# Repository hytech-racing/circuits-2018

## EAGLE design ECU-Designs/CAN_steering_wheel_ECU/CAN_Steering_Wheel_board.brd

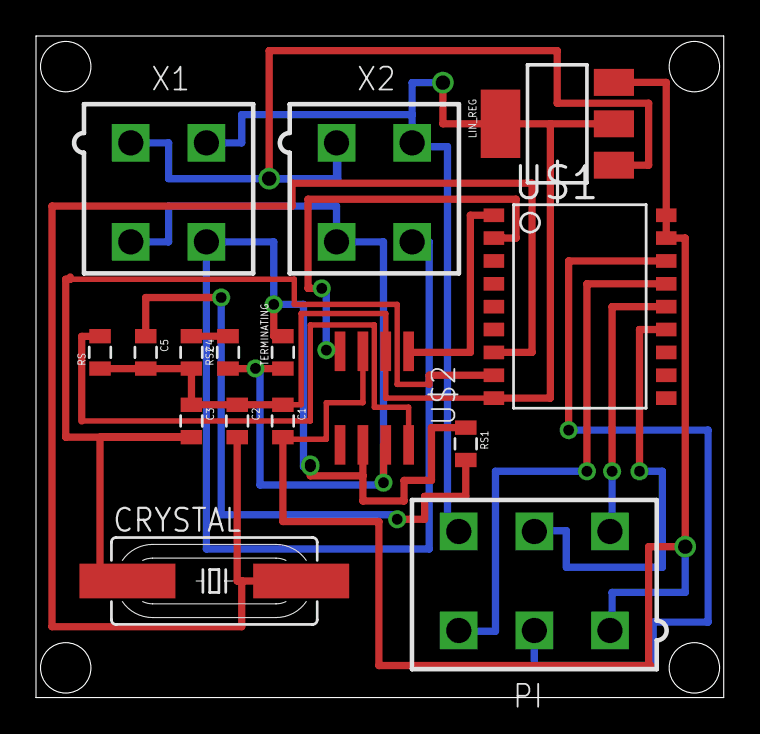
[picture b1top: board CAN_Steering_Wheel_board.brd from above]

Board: 2 copper layers, 38.2 x 36.8 mm, 16 parts (0 on the bottom side), 16 nets.

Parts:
C1: 0.1uF; 0805
C2, C3: 22pF; 0805
C4, C5: 560pF; 0805
CRYSTAL: 16MHz; HC49UP
LIN_REG: SOT223
PI: MINIFIT_5566-6
RS: 4.7k; 0805
RS1, RS2: 100; 0805
TERMINATING: 120; 0805
U$1: MCP2515SMD; SOIC-18W
U$2: MCP2551; SOIC-08
X1, X2: MINIFIT_5566-4

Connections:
5V: C1.2, LIN_REG.3, PI.1, U$1.17, U$1.18, U$2.3
12V: LIN_REG.1, X1.1, X2.1
CANH: RS2.1, TERMINATING.1, U$2.7, X1.3, X2.3
CANL: RS1.1, TERMINATING.2, U$2.6, X1.4, X2.4
GND: C1.1, C2.1, C3.1, C4.2, C5.2, LIN_REG.2, LIN_REG.4, PI.6, RS.1, U$1.9, U$2.2, X1.2, X2.2
unnamed: U$1.1, U$2.1
unnamed: U$1.2, U$2.4
unnamed: C3.2, CRYSTAL.1, U$1.8
unnamed: PI.2, U$1.16
unnamed: PI.3, U$1.15
unnamed: PI.4, U$1.14
unnamed: PI.5, U$1.13
unnamed: RS.2, U$2.8
unnamed: C2.2, CRYSTAL.2, U$1.7
unnamed: C4.1, RS2.2
unnamed: C5.1, RS1.2

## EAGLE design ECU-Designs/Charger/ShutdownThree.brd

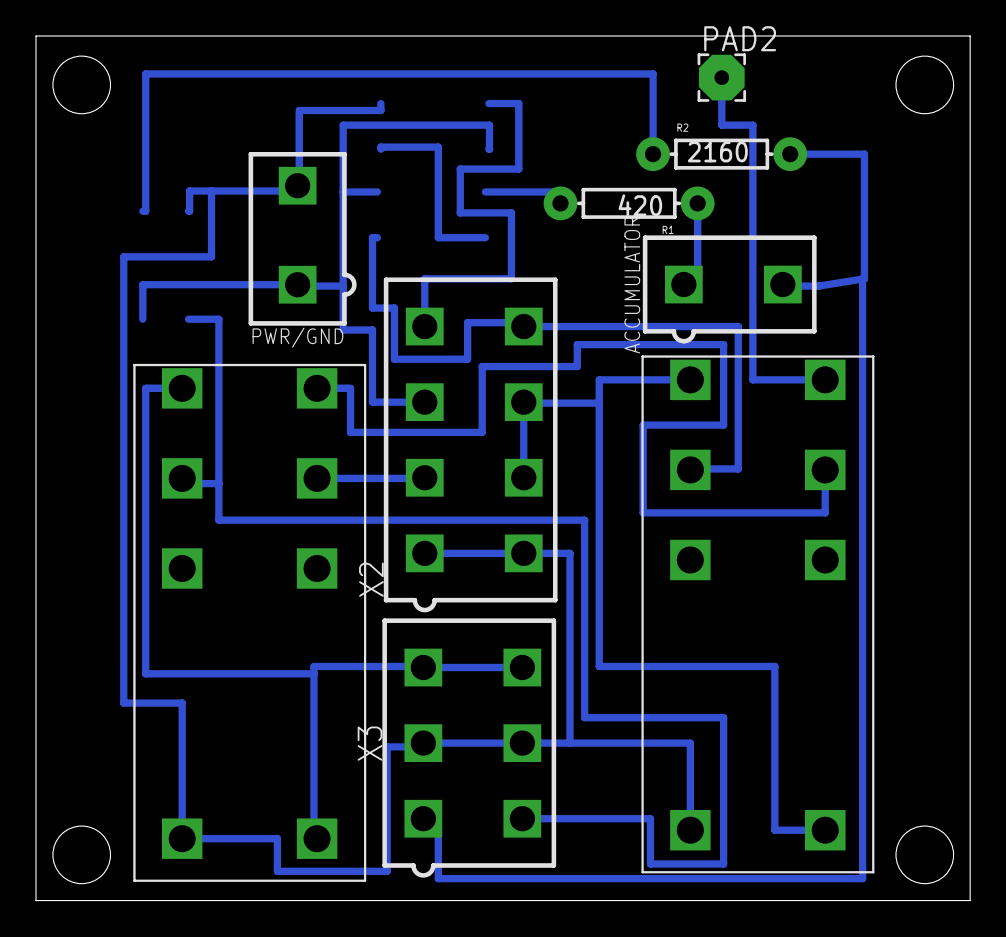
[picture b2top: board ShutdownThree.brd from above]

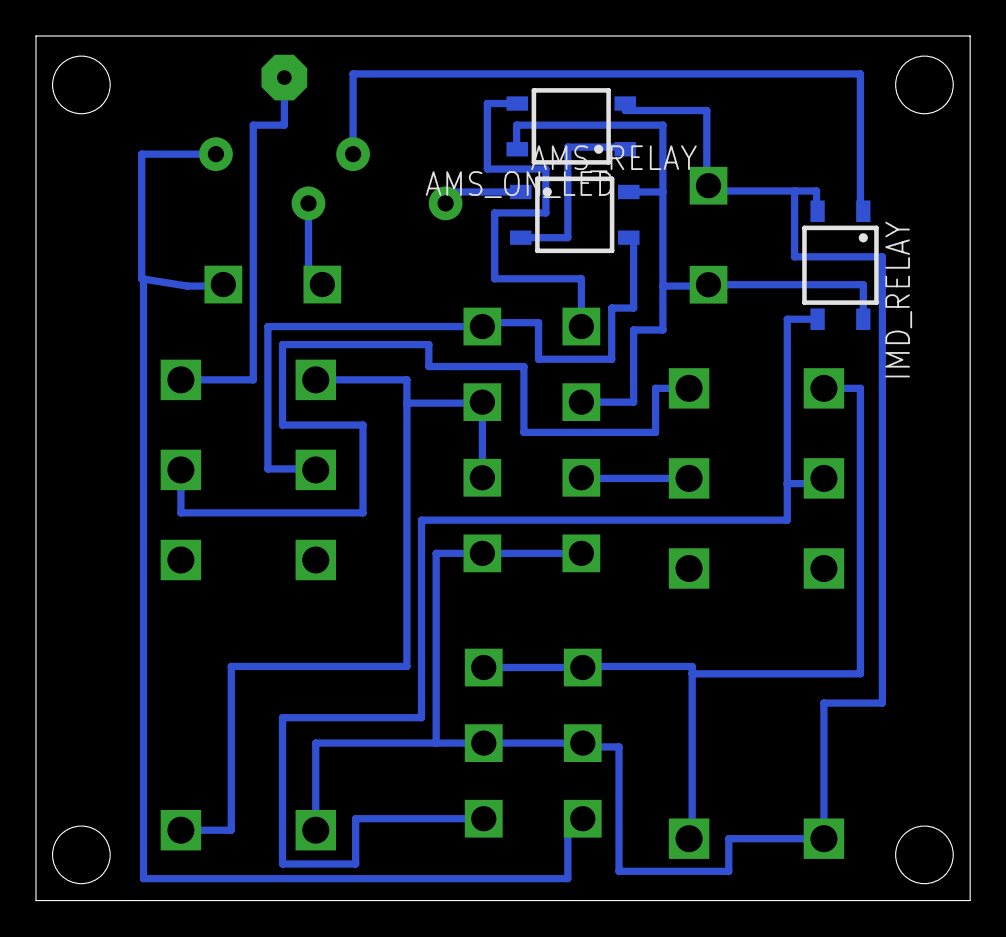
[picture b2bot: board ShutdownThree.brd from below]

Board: 2 copper layers, 51.9 x 48.0 mm, 12 parts (3 on the bottom side), 15 nets.

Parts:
ACCUMULATOR: CONNECTOR-2; MINIFIT_5566-2
AMS_ON_LED: CPC1002N; SOP04
AMS_RELAY: CPC1002N; SOP04
IMD: G2RL-2-DC12; G2RL-2
IMD_RELAY: CPC1002N; SOP04
PAD2: WIREPAD2,54/0,8; 2,54/0,8
PWR/GND: MINIFIT_5566-2
R1: 420; AXIAL-0.3EZ
R2: 2160; AXIAL-0.3EZ
U$7: G2RL-2-DC12; G2RL-2
X2: CONNECTOR-8; MINIFIT_5566-8
X3: CONNECTOR-6; MINIFIT_5566-6

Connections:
+12V: AMS_ON_LED.4, AMS_RELAY.4, IMD_RELAY.4, PWR/GND.1, X2.3
AMS: ACCUMULATOR.1, R1.P$1
GND: AMS_ON_LED.2, IMD.COIL+, IMD_RELAY.2, PWR/GND.2, U$7.COIL+, X2.1, X2.5, X3.2, X3.5
IMD: ACCUMULATOR.2, R2.P$2, X3.1
unnamed: IMD.6, X2.2
unnamed: IMD.5, U$7.6
unnamed: AMS_ON_LED.3, X2.4
unnamed: AMS_RELAY.1, R1.P$2
unnamed: AMS_RELAY.3, U$7.3, X2.8
unnamed: PAD2.1, U$7.5
unnamed: IMD.3, IMD_RELAY.3, X3.4
unnamed: IMD_RELAY.1, R2.P$1
unnamed: U$7.4, U$7.COIL-, X2.6, X2.7
unnamed: IMD.4, IMD.COIL-, X3.3, X3.6
unnamed: AMS_ON_LED.1, AMS_RELAY.2

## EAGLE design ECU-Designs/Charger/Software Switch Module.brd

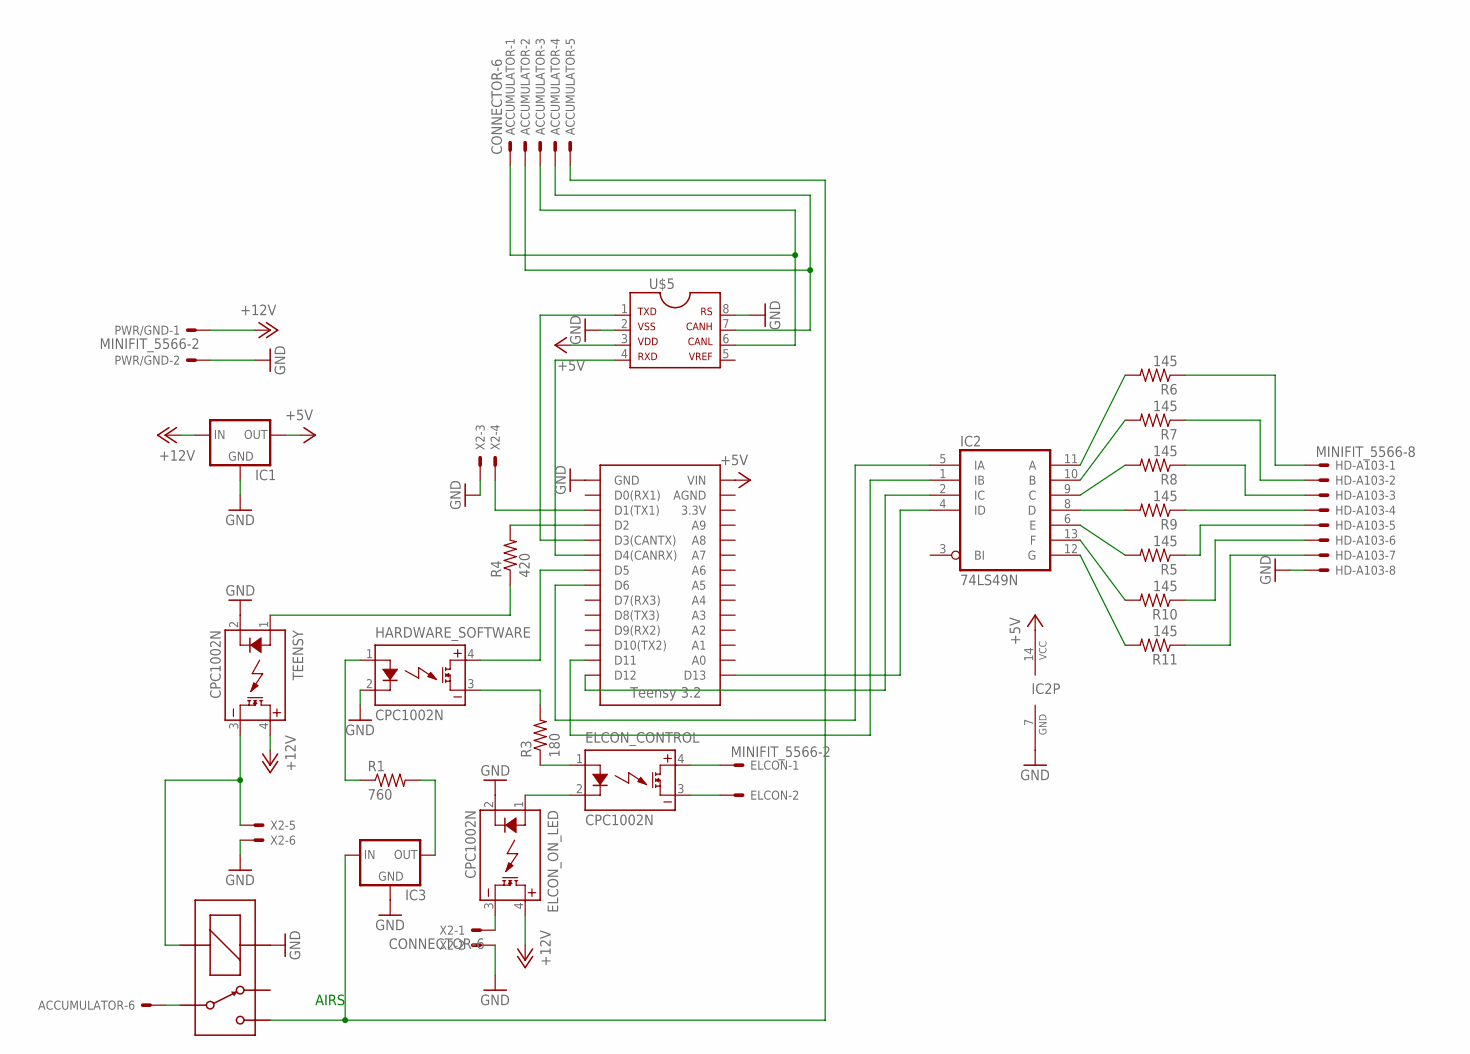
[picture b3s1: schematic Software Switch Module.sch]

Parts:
ACCUMULATOR: CONNECTOR-6; MINIFIT_5566-6
ELCON: MINIFIT_5566-2
ELCON_CONTROL: CPC1002N; SOP04
ELCON_ON_LED: CPC1002N; SOP04
HARDWARE_SOFTWARE: CPC1002N; SOP04
HD-A103: MINIFIT_5566-8
IC1, IC3: 5VREG_L7805_VERT; TO-220
IC2: 74LS49N; DIL14
PWR/GND: MINIFIT_5566-2
R1: 760; AXIAL-0.3
R3: 180; AXIAL-0.3EZ
R4: 420; AXIAL-0.3EZ
R5, R6, R7, R8, R9, R10, R11: 145; AXIAL-0.3EZ
TEENSY: CPC1002N; SOP04
U$1: TEENSY_3.2_SIMPLE
U$2: G5LE; ZF112
U$5: MCP2551; SOIC-08
X2: CONNECTOR-6; MINIFIT_5566-6

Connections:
+5V: IC1.3 (OUT), IC2.14 (VCC), U$1.VIN, U$5.3
+12V: ELCON_ON_LED.4 (DC+), IC1.1 (IN), PWR/GND.1, TEENSY.4 (DC+)
AIRS: ACCUMULATOR.5, IC3.1 (IN), U$2.S
GND: ELCON_ON_LED.2 (CONTROL-), HARDWARE_SOFTWARE.2 (CONTROL-), HD-A103.8, IC1.2 (GND), IC2.7 (GND), IC3.2 (GND), PWR/GND.2, TEENSY.2 (CONTROL-), U$1.GND, U$2.1 (COIL+), U$5.2, U$5.8, X2.2, X2.3, X2.6
unnamed: R4.P$1 (1), TEENSY.1 (CONTROL+)
unnamed: HARDWARE_SOFTWARE.1 (CONTROL+), R1.P$1 (1)
unnamed: HARDWARE_SOFTWARE.4 (DC+), U$1.D5
unnamed: ACCUMULATOR.6, U$2.P
unnamed: IC3.3 (OUT), R1.P$2 (2)
unnamed: ELCON_CONTROL.1 (CONTROL+), R3.P$1 (1)
unnamed: ELCON.1, ELCON_CONTROL.4 (DC+)
unnamed: ELCON.2, ELCON_CONTROL.3 (DC-)
unnamed: U$1.D1(TX1), X2.4
unnamed: U$1.D4(CANRX), U$5.4
unnamed: R4.P$2 (2), U$1.D2
unnamed: U$1.D3(CANTX), U$5.1
unnamed: ACCUMULATOR.1, ACCUMULATOR.3, U$5.6
unnamed: TEENSY.3 (DC-), U$2.2 (COIL-), X2.5
unnamed: IC2.11 (A), R6.P$2 (2)
unnamed: HARDWARE_SOFTWARE.3 (DC-), R3.P$2 (2)
unnamed: ELCON_CONTROL.2 (CONTROL-), ELCON_ON_LED.1 (CONTROL+)
unnamed: ELCON_ON_LED.3 (DC-), X2.1
unnamed: IC2.5 (IA), U$1.D6
unnamed: IC2.1 (IB), U$1.D11
unnamed: IC2.4 (ID), U$1.D13
unnamed: IC2.2 (IC), U$1.D12
unnamed: IC2.10 (B), R7.P$2 (2)
unnamed: IC2.9 (C), R8.P$2 (2)
unnamed: IC2.8 (D), R9.P$2 (2)
unnamed: IC2.13 (F), R10.P$2 (2)
unnamed: IC2.12 (G), R11.P$2 (2)
unnamed: IC2.6 (E), R5.P$2 (2)
unnamed: HD-A103.1, R6.P$1 (1)
unnamed: ACCUMULATOR.2, ACCUMULATOR.4, U$5.7
unnamed: HD-A103.2, R7.P$1 (1)
unnamed: HD-A103.3, R8.P$1 (1)
unnamed: HD-A103.4, R9.P$1 (1)
unnamed: HD-A103.5, R5.P$1 (1)
unnamed: HD-A103.6, R10.P$1 (1)
unnamed: HD-A103.7, R11.P$1 (1)

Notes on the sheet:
AIRS

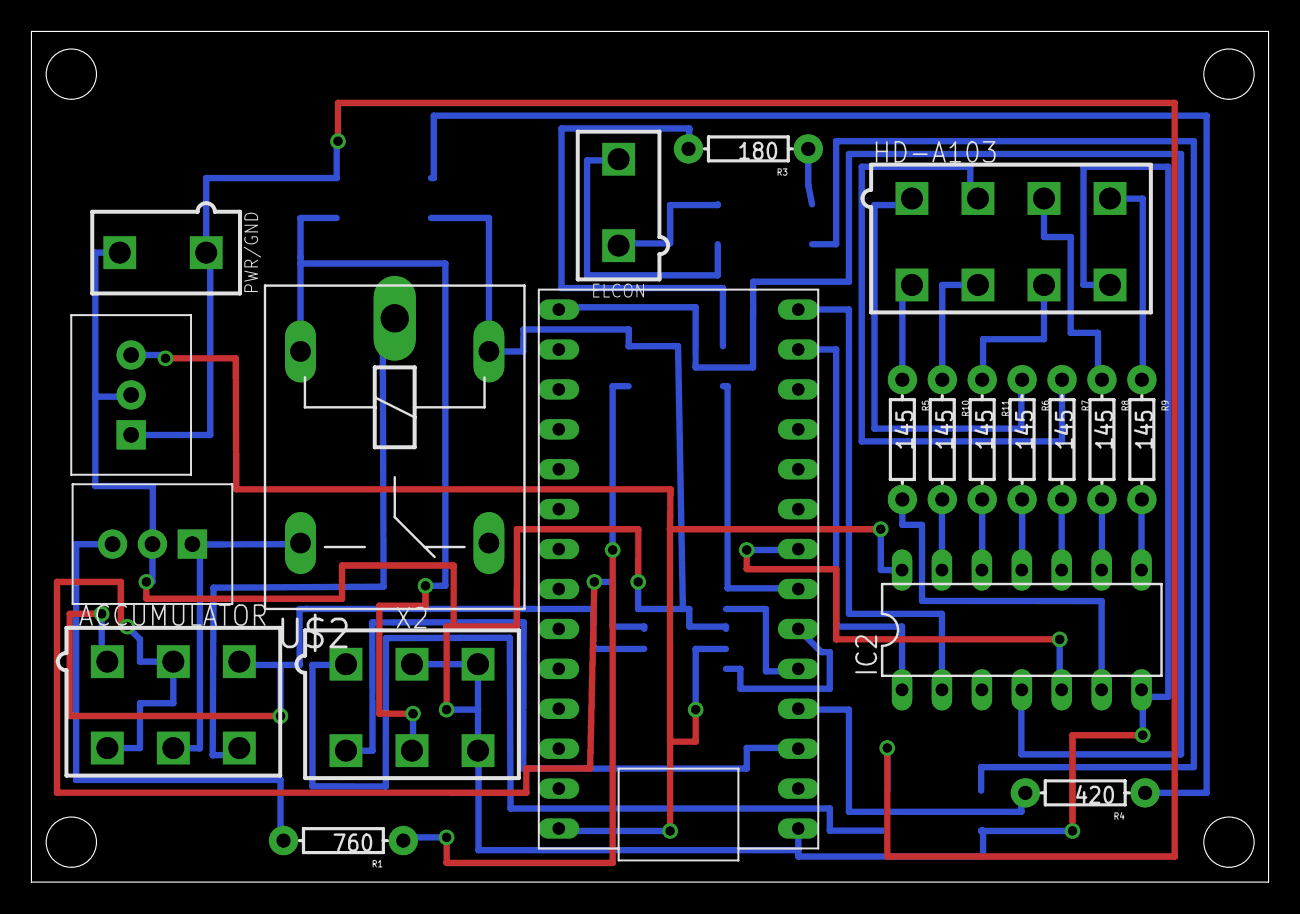
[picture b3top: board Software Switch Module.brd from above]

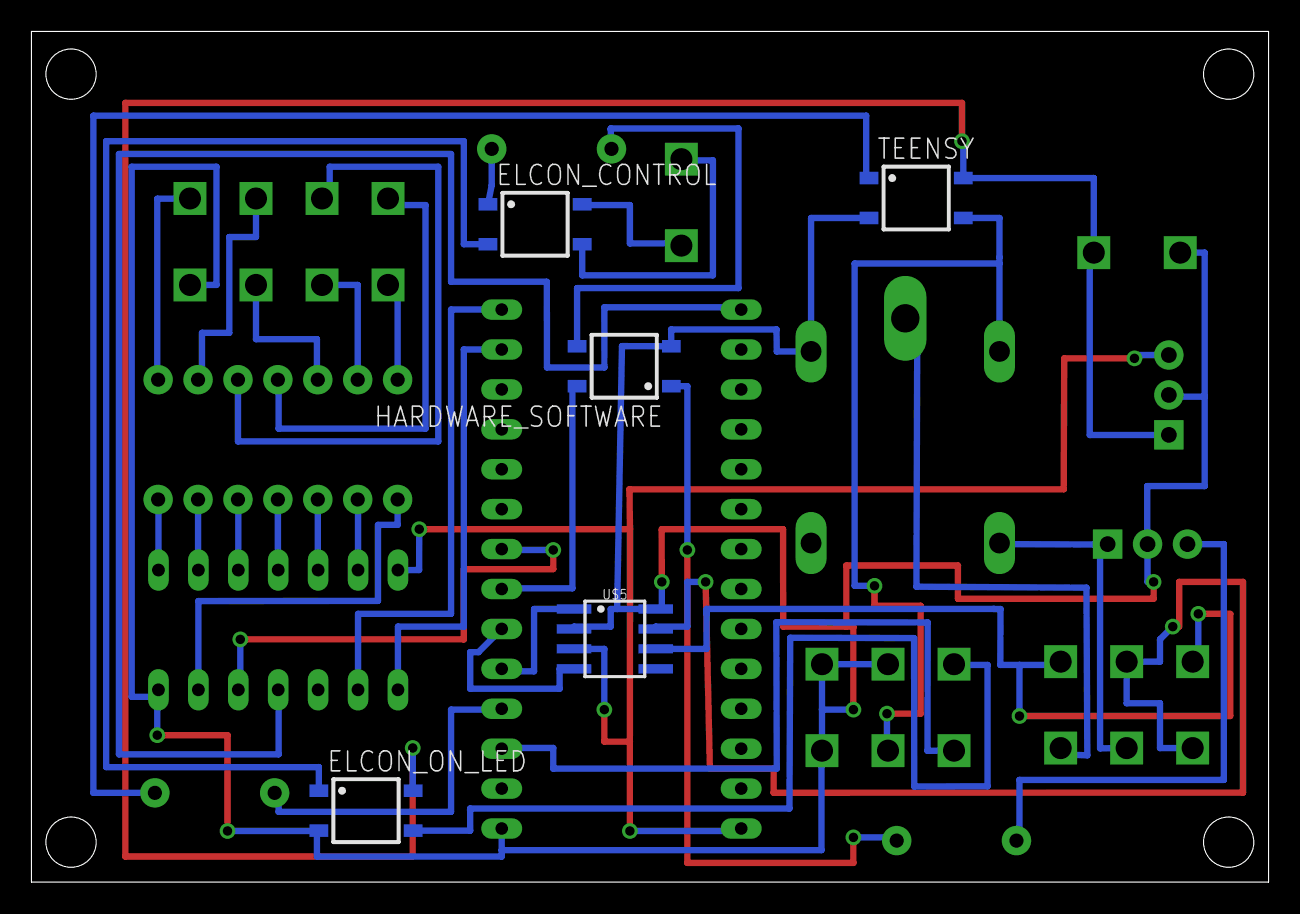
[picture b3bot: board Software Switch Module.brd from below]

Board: 2 copper layers, 78.7 x 54.1 mm, 25 parts (5 on the bottom side), 40 nets.

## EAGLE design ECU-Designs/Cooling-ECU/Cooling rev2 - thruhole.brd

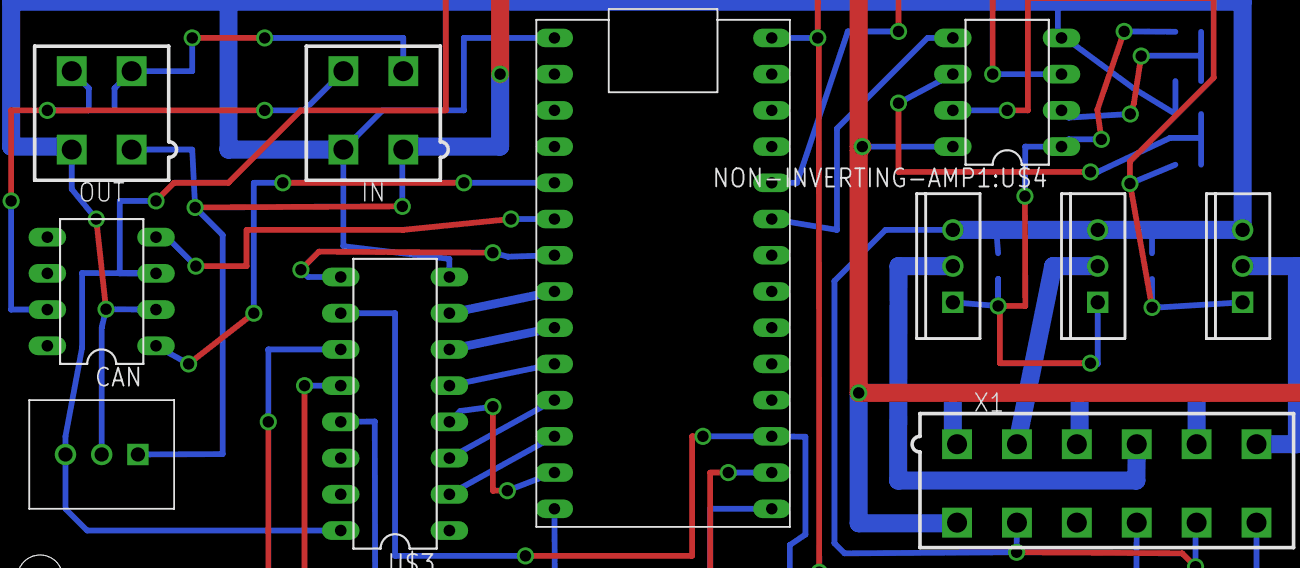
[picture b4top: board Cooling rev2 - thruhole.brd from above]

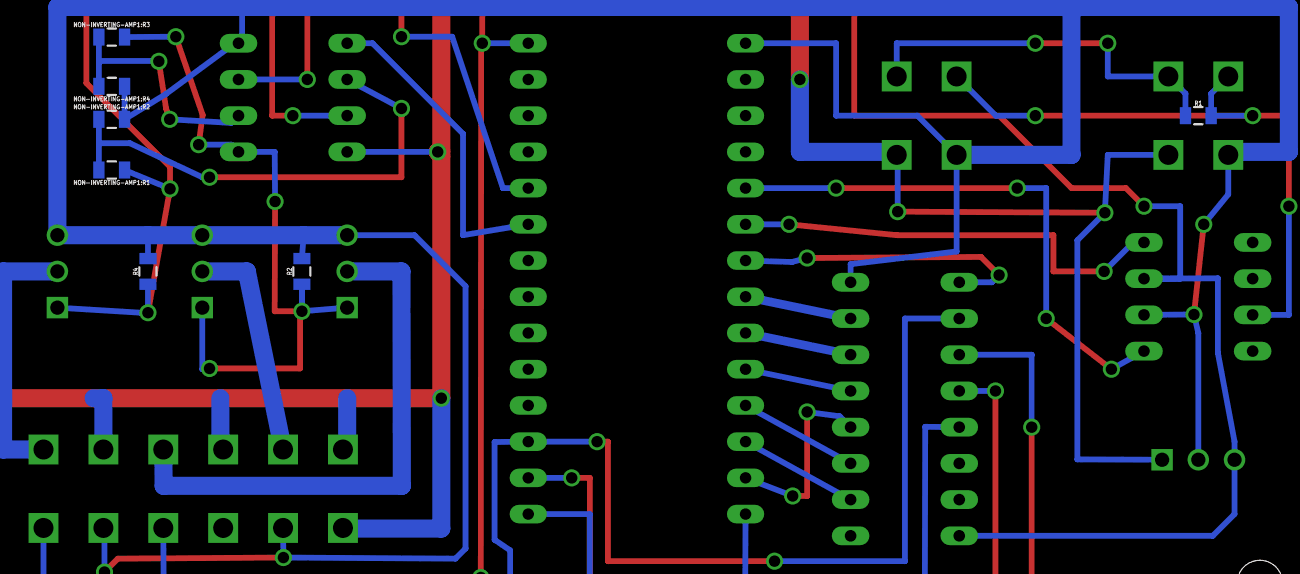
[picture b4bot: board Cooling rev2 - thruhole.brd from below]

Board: 2 copper layers, 18 parts (7 on the bottom side), 27 nets.

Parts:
CAN: MCP2551DIL; DIL08
IC1: TO-220-SPACED
IN: MINIFIT_5566-4
NON-INVERTING-AMP1:R1, NON-INVERTING-AMP1:R2, NON-INVERTING-AMP1:R3, NON-INVERTING-AMP1:R4: 0805
NON-INVERTING-AMP1:U$4: MCP6002PDIP; DIL08
OUT: MINIFIT_5566-4
R1: 120; 0805
R2, R4: 0805
T1, T2, T3: N-CHANNEL_MOSFETGENERIC_SPACED; TO-220-SINK-SPACED
U$1: TEENSY_3.2_SIMPLE
U$3: CD4040B; DIL16
X1: MINIFIT_5566-12

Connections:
+5V: CAN.3, IC1.3, U$1.VIN, U$3.16, X1.10
+12V: IC1.1, IN.1, NON-INVERTING-AMP1:U$4.8, OUT.1, X1.1, X1.3, X1.5, X1.7
FAN1-: T1.2, X1.2
FAN2-: T2.2, X1.4
FAN3-: T3.2, X1.6
GND: CAN.2, IC1.2, IN.2, NON-INVERTING-AMP1:R2.2, NON-INVERTING-AMP1:R4.1, NON-INVERTING-AMP1:U$4.4, OUT.2, R2.2, R4.2, T1.3, T2.3, T3.3, U$1.GND, U$3.8, X1.8, X1.11
unnamed: NON-INVERTING-AMP1:R3.2, NON-INVERTING-AMP1:U$4.1, R2.1, T1.1, T2.1
unnamed: CAN.1, U$1.D3(CANTX)
unnamed: CAN.4, U$1.D4(CANRX)
unnamed: NON-INVERTING-AMP1:U$4.3, U$1.A8
unnamed: NON-INVERTING-AMP1:R1.1, NON-INVERTING-AMP1:U$4.7, R4.1, T3.1
unnamed: IN.3, OUT.3, R1.1
unnamed: CAN.7, IN.4, OUT.4, R1.2
unnamed: U$1.D5, U$3.9
unnamed: U$1.D6, U$3.7
unnamed: U$1.D7(RX3), U$3.6
unnamed: U$1.D8(TX3), U$3.5
unnamed: U$1.D9(RX2), U$3.3
unnamed: U$1.D10(TX2), U$3.2
unnamed: NON-INVERTING-AMP1:U$4.5, U$1.A7
unnamed: U$1.D11, U$3.4
unnamed: U$1.D12, U$3.13
unnamed: U$1.A0, U$3.11
unnamed: U$1.D13, U$3.12
NON-INVERTING-AMP1:N$2: NON-INVERTING-AMP1:R1.2, NON-INVERTING-AMP1:R2.1, NON-INVERTING-AMP1:U$4.6
NON-INVERTING-AMP1:N$4: NON-INVERTING-AMP1:R3.1, NON-INVERTING-AMP1:R4.2, NON-INVERTING-AMP1:U$4.2
PULSE: U$1.A1, U$3.10, X1.12

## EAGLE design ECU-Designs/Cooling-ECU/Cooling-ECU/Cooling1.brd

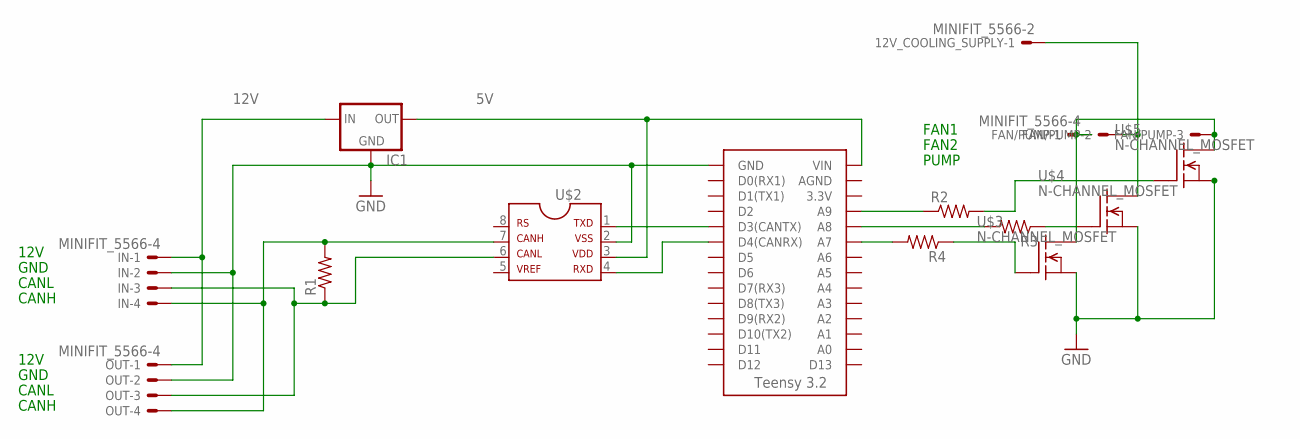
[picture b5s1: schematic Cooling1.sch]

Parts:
12V_COOLING_SUPPLY: MINIFIT_5566-2
FAN/PUMP: MINIFIT_5566-4
IC1: 5V_REGULATOR_LM340-NLM340MPX-5.0/NOPB; SOT223
IN: MINIFIT_5566-4
OUT: MINIFIT_5566-4
R1, R2, R3, R4: RESISTOR0805-RES; 0805
U$1: TEENSY_3.2_SIMPLE
U$2: MCP2551SOIC; SOIC08

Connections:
5V: U$1.VIN, U$2.3
12V: IC1.3 (IN), IN.1, OUT.1
12V_COOLING_SUPPLY: FAN/PUMP.1, FAN/PUMP.3
GND: IC1.1 (GND), IN.2, OUT.2, U$1.GND, U$2.2
unnamed: R4.2, U$1.A7
unnamed: U$1.D3(CANTX), U$2.1
unnamed: U$1.D4(CANRX), U$2.4
unnamed: IN.3, OUT.3, R1.1
unnamed: R2.1, U$1.A9
unnamed: 12V_COOLING_SUPPLY.1, FAN/PUMP.2
unnamed: IN.4, OUT.4, R1.2, U$2.7
unnamed: R3.2, U$1.A8

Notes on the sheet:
12V
GND
CANL
CANH
FAN1
FAN2
PUMP

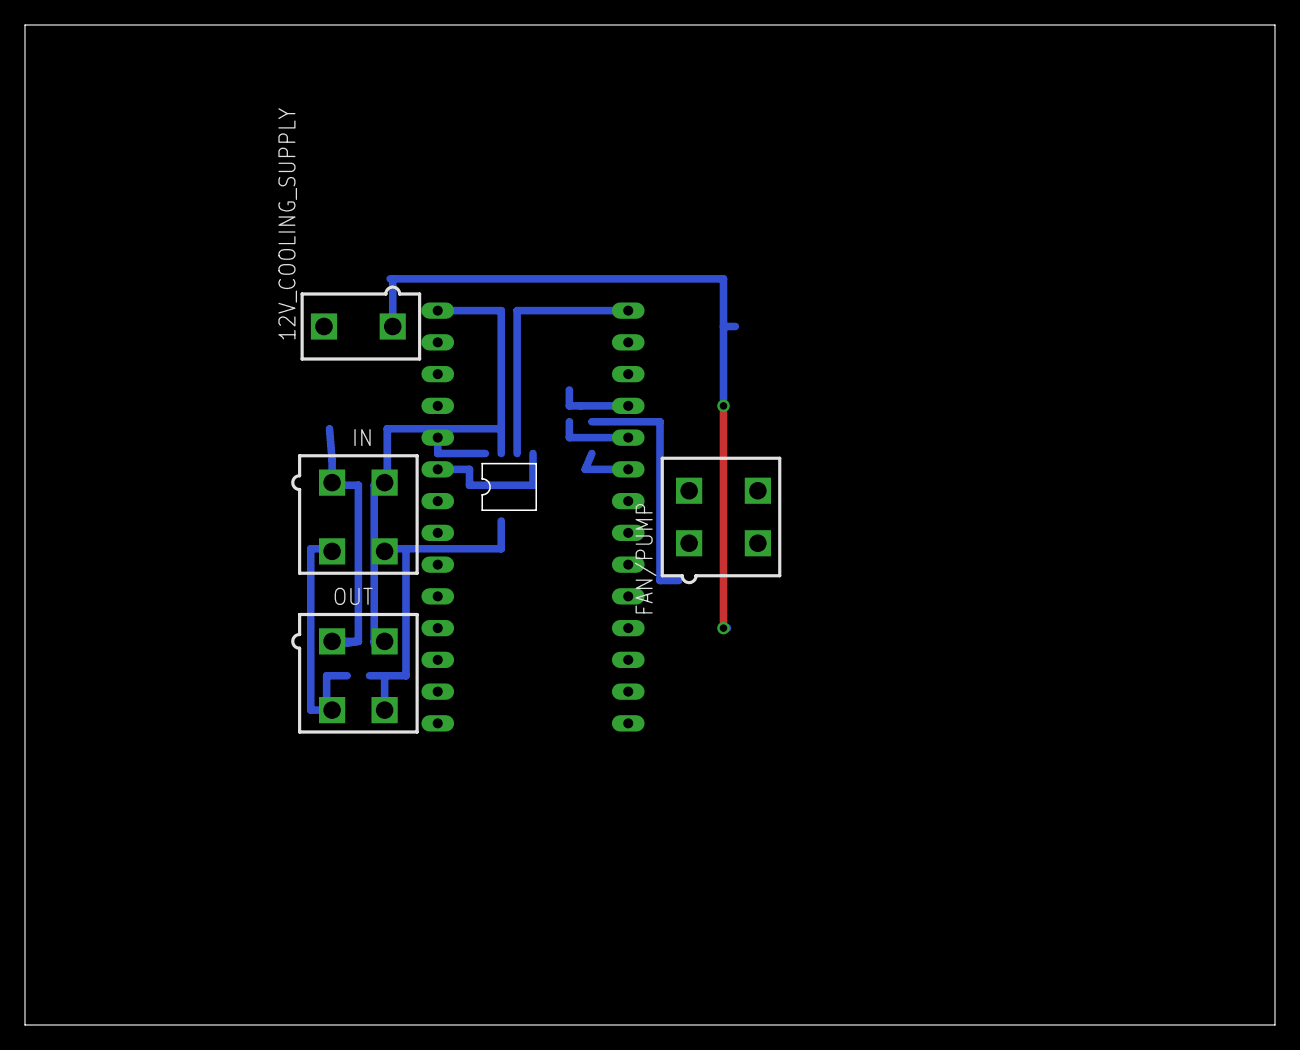
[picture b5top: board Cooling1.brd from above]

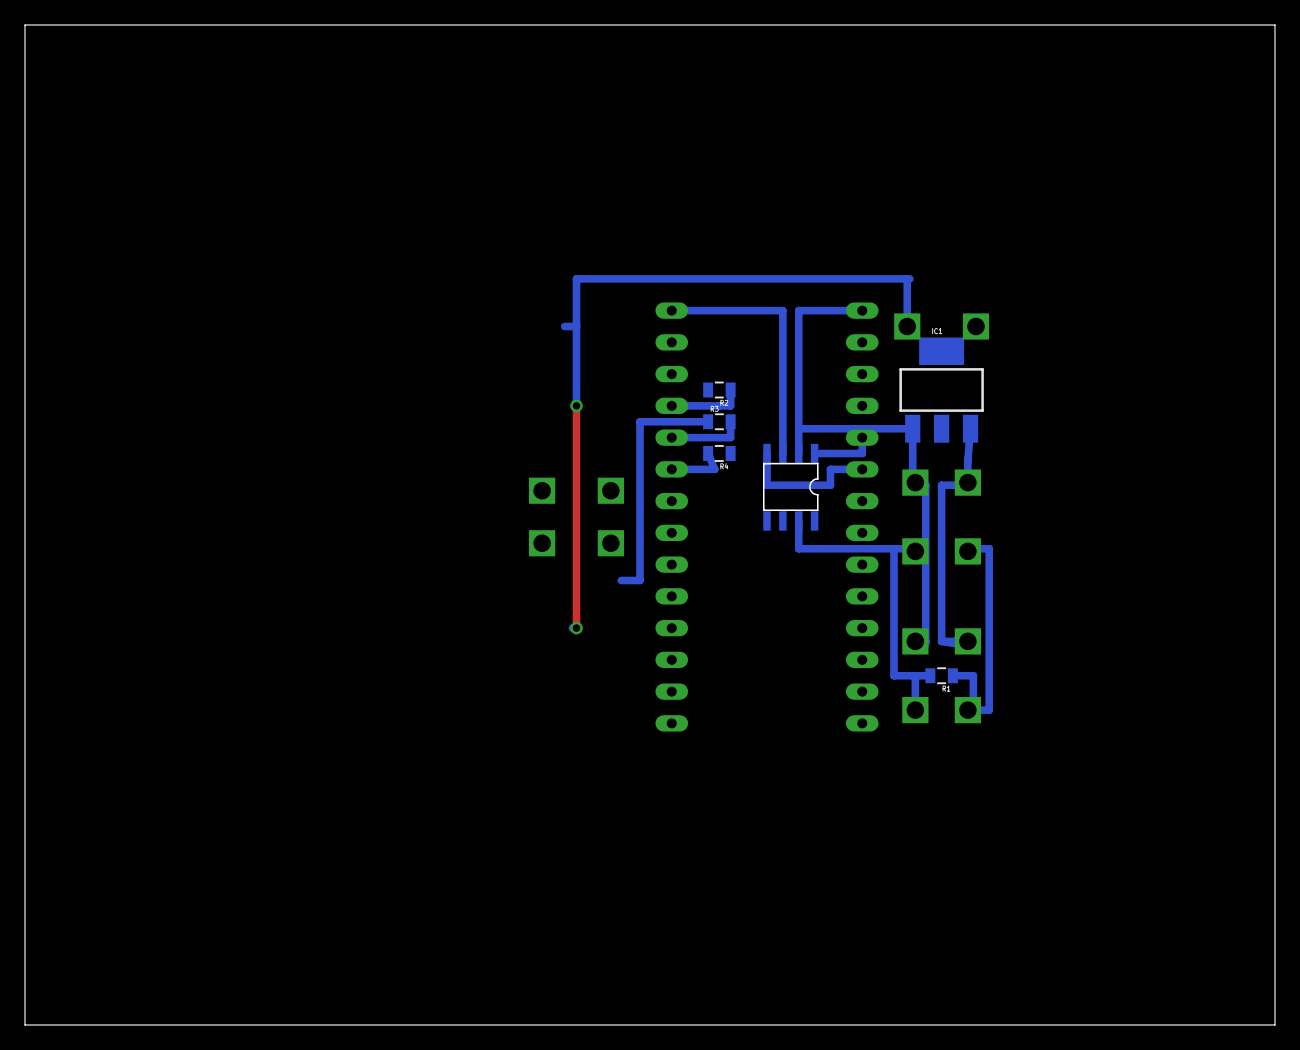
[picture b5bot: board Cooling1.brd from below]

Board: 2 copper layers, 100.0 x 80.0 mm, 11 parts (6 on the bottom side), 12 nets.
